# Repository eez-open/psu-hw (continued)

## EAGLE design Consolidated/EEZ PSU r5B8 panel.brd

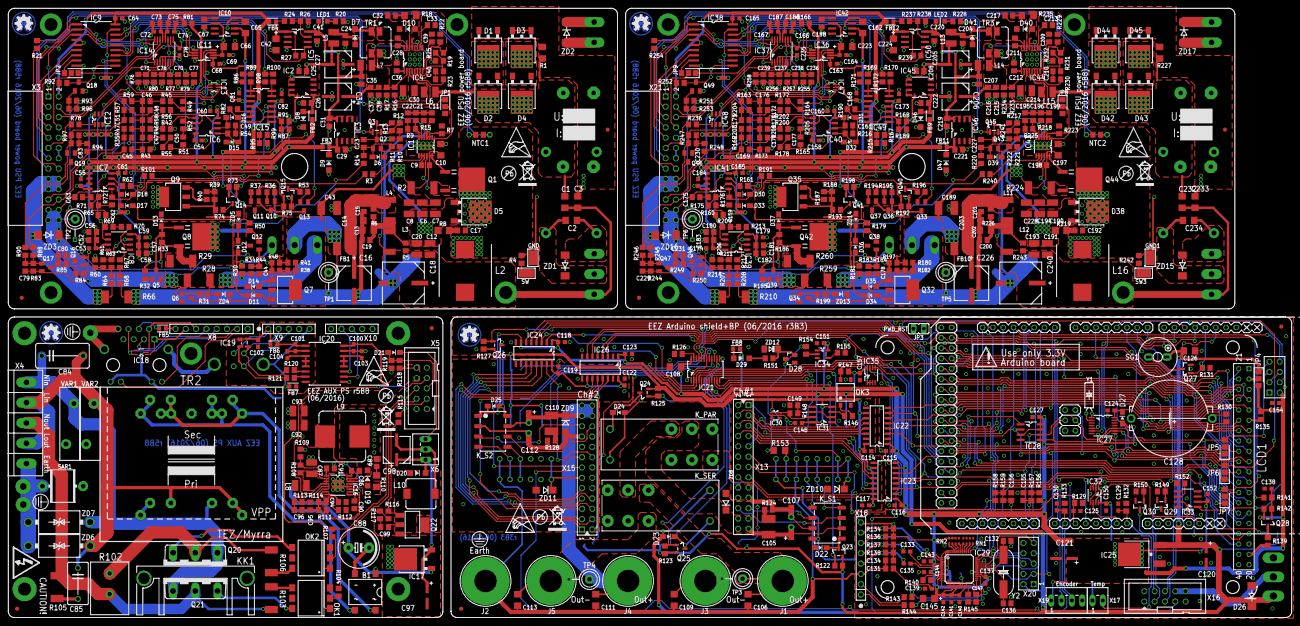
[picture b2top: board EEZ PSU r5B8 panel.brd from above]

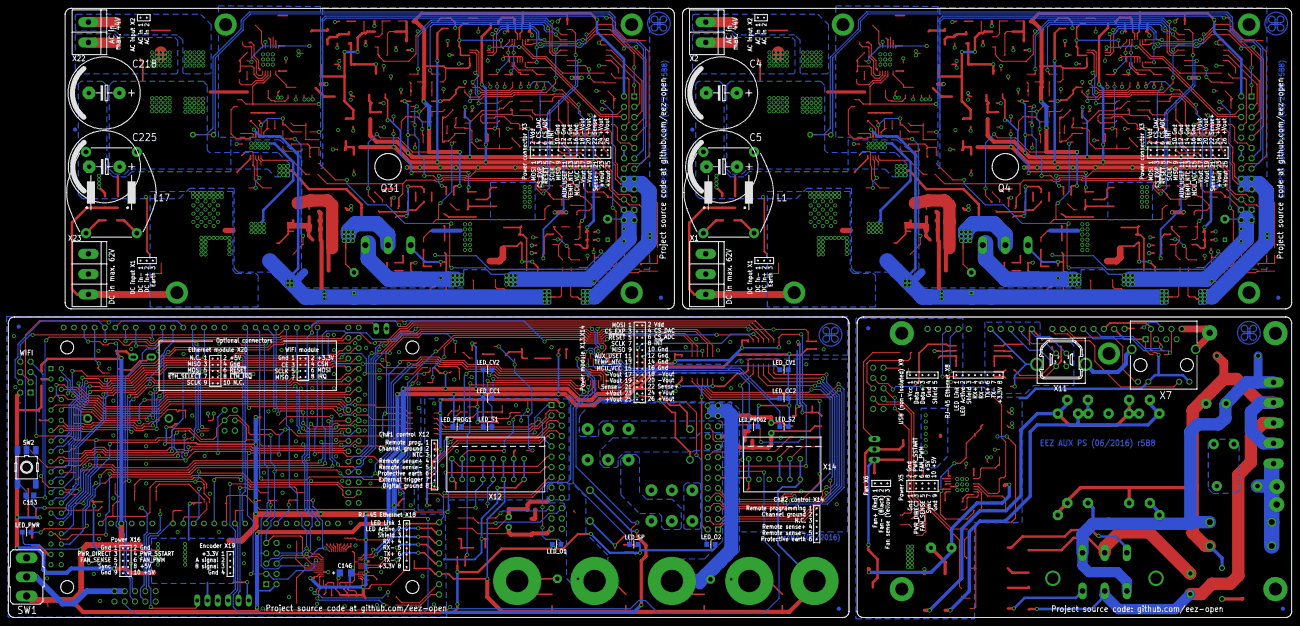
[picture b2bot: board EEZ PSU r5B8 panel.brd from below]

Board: 3 copper layers, 316.0 x 150.0 mm, 809 parts (28 on the bottom side), 562 nets.

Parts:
B1: DF01S; DFS
C1, C2, C3, C232, C233, C234: 100n; C1206
C4, C5, C218, C225: 2m2; ECAP7.5/18
C6, C7, C8, C87, C92, C93, C190, C194, C228: 4u7; C1210
C9, C198: 470n; C0805
C10, C13, C14, C197, C202, C203: 1u; C1206
C11, C15, C19, C26, C29, C36, C41, C91, C199, C200, C201, C212, C220, C221, C222: 100n; C0805
C12, C20, C191, C193: 10u; C1210
C16, C226: EEEFK1J470P; CAPAE830X1050N
C17, C32, C89, C192, C217: 330p; C0805
C18, C240: EEEFK1J101P; PANASONIC_F
C21, C49, C161, C196: 120p; C0805
C22, C195: 4n7; C0805
C23, C227: 470p; C0805
C24, C35, C37, C38, C204, C207, C215, C216: 2u2; C0805
C25, C31, C208, C219: 330n; C0805
C27, C34, C205, C206: 47u; CAPAE660X610N
C28, C86, C90, C131, C211: 22n; C0805
C30, C214: 2u2/100V; C1210
C33, C44, C52, C57, C79, C83, C134, C147, C155, C156, C178, C181, C183, C213, C229, C230: 10n; C0805
C39, C70, C71, C76, C77, C209, C236, C237, C238, C239: 3n3; C0805
C40, C46, C50, C62, C63, C94, C159, C175, C176, C177, C210: 1n; C0805
C42, C146, C224: 4u7; EC1206
C43, C189: 470n; C1812
C45, C51, C169, C171: 47p; C0805
C47, C48, C80, C170, C172, C231: 2n2; C0805
C53, C54, C55, C59, C60, C61, C64, C68, C69, C72, C74, C78, C81, C82, C100, C101, C102, C103, C104, C114, C115, C116, C117, C118, C119, C122, C123, C124, C125, C127, C129, C130, C137, C138, C139, C140, C141, C142, C143, C144, C148, C150, C151, C152, C154, C157, C158, C160, C163, C164, C165, C166, C167, C168, C173, C174, C179, C184, C185, C235: 100n; C0603
C56, C58, C67, C73, C75, C180, C182, C186, C187, C188: 1u; C0805
C65, C108, C126, C162: 10u; C1206
C66, C145, C223: 10u; EC1206
C84: 6n8 (X1); C102-064X133
C85: 47n/400V; C075-052X106
C88: 1mF/25V; ECAP5/10.5
C95: 3n9; C0805
C96: 180p; C0805
C97, C121: 10u; PANASONIC_C
C98: 100u; CAPAE660X610N
C99, C149, C153: 47n; C0805
C105, C110: 470n/100V; C1812
C106, C109, C111, C113: 10n; C1206
C107, C112: UPW1J150MED; CAPAE660X610N_COMBO2
C120: 47u; PANASONIC_C
C128: EECS5R5H105; SG-R20MM
C132, C136: 18p; C0805
C133, C135: 6n8; C0603
D1, D2, D3, D4, D42, D43, D44, D45: STPS15H100; TO252@1
D5, D38: STPS15H100; TO252
D6, D11, D12, D13, D14, D15, D16, D17, D18, D21, D22, D23, D24, D25, D27, D30, D31, D32, D33, D34, D35, D36, D37, D39: BAS316; SOD323-W
D7, D10, D19, D40, D41: DFLS1100-7; SOD123
D8, D9, D20, D29, D46, D47: SKL16; SOD123
D26: SMBJ5.0A-TR; DO214AA
D28: BAT54S; SOT23
EEZ_SIGNATURE, EEZ_SIGNATURE1, EEZ_SIGNATURE2, EEZ_SIGNATURE3: SIGNATURESMALL; SIGNATURE_5MM
FB1, FB10: 2743019447; L1812
FB2, FB3, FB4, FB5, FB6, FB7, FB8, FB9, FB11, FB12: 60R@100MHz; BEAD0603
GND, GND1: S1751-46R
IC1, IC43: LTC3864; LTC_05-08-1666
IC2, IC45: MC79L05; SOIC127P600X173-8N
IC3, IC46: MC78L05; SOIC127P600X173-8N
IC4, IC44: LM5574; SOP65P640X110-16N
IC5, IC50: LP2951SO8; SOIC127P600X175-8N
IC6, IC7, IC40, IC41: TL072D; SOIC127P600X173-8N
IC8, IC39: OP27GSZ; SOIC127P600X173-8N
IC9, IC38: MCP23S08-E/SO; SOIC127P1030X265-18N
IC10, IC42: REF5025; SOIC127P600X175-8N
IC11, IC36: DAC8552; DGK8-M
IC12, IC48: ADG465SOT-23; SOT95P280X145-6N
IC13, IC47: TS5A9411DCKT; SOT65P210X110-6N
IC14, IC37: ADS1120; PW(R-PDSO-G16)
IC15, IC49: LP339D; SOIC127P600X175-14N
IC16: LM25575; SOP65P640X110-17N
IC17: MC7812; TO252
IC18: TPD4E002DRLR; SOT50P280X60-5N
IC19: TPD2E001DZDR; SOP192P292X122-4N
IC20: ADUM3160BRWZ; SOIC-16W
IC21: TLC5925IDBQR; SOP63P600X175-24N
IC22, IC26: Si8641EC-B-IS1; SOIC-16
IC23, IC24: SI8651EC-B-IS1; SOIC-16
IC25: LD1117ADT33TR; DPACK
IC27: PCA21125; SOP65P640X120-14N
IC28: AT25256B; SOIC127P600X175-8N
IC29: W5500; TQFP48-7X7
IC30: BC857BS; SOT65P210X110-6N
IC31: TLC555; SOIC127P600X175-8N
IC32: SN74LVC2G08DCTR; SOP65P400X130-8N
IC33: TPS3705-33D; SOIC127P600X175-8N
IC34: SN74LV1T34DBVR; SOT95P280X145-5N
IC35: SN74LVC2G02DCTR; SOP65P400X130-8N
J1, J4: BS-244DSM-R; BP_5_12
J2: BS-244DSM-G; BP_5_12
J3, J5: BS-244DSM-B; BP_5_12
JP1, JP2, JP4, JP5, JP6, JP7, JP8, JP9: 0R-JUMPA; A0R-JMP
JP3: 826926-2; JP1
KK1: SK 145/37,5; SK145
K_PAR: RT424005; RT-C/016A5_ROUND
K_S1, K_S2: G6K-2F-5DC; G6K-2F
K_SER: RT424005; RT-C/016A5_ROUND
L1, L17: RN114-4/02; RN114
L2, L16: 7443551331; WE-HCI_1350/1365
L3, L4, L11, L12: IHLP2020CZER3R3M11; IHLP-2020BZ-11
L5, L6, L7, L8, L13, L14, L15: 2u2; L1210
L9: 100uH (MSS1260-104K); MSS1278
L10: 470u; DE0704
LCD1: TFT_320QVT; LCD_TFT_320QVT_MIRROR
LED1, LED2: HSMY-C170; LED_0805
LED_CC1, LED_CC2: HSMH-C170; LED_0805
LED_CV1, LED_CV2: HSMY-C170; LED_0805
LED_O1, LED_O2: HSMG-C170; LED_0805
LED_PROG1, LED_PROG2: HSMH-C170; LED_0805
LED_PWR: HSMR-C170; LED_0805
LED_S1, LED_S2: HSMY-C170; LED_0805
LED_SP: HSMH-C170; LED_0805
MCU: Arduino Due; ARDUINO+ICSP_MIRROR
NTC1, NTC2: 10K/Beta:3570K; R_0204/5+0805
OK1: MOC3052; DIL6-SMD
OK2: MOC3062; DIL6-SMD
OK3: HCPL-181
Q1, Q44: SUD19P06-60; TO229P990X239-3N
Q2, Q10, Q11, Q17, Q36, Q37, Q43, Q47: MMBT5401; SOT23-BEC
Q3, Q15, Q27, Q29, Q30, Q40, Q45: 2N7002; SOT103P240X110-3N
Q4, Q31: IRFP250N; TO247BH-CLR
Q5, Q39: BC857C; SOT23-BEC
Q6, Q34: BC846C; SOT23-BEC
Q7, Q9, Q32, Q35: BCP56-16.115; SOT230P700X180-4N
Q8, Q42: IRFR5410; TO229P990X239-3N
Q12, Q13, Q16, Q18, Q19, Q33, Q38, Q46, Q48, Q49: MMBT5551; SOT23-BEC
Q14, Q41: BSS84P; SOT95P237X112-3N
Q20, Q21: BTA26-600; TOP3S-1
Q22: IRLL014N; SOT223
Q23, Q24, Q25, Q26, Q28: IRLML2246TRPBF; SOT95P237X112-3N
R1, R227: 12K; R1206
R2, R224: R010/2W; R2512
R3, R13, R21, R54, R152, R216, R240, R241, R254: 0R; R0805
R4, R31, R39, R78, R117, R154, R155, R188, R199, R236, R242: 1K; R0805
R5, R6, R41, R115, R151, R180, R226, R243: 100R; R0805
R7, R84, R85, R87, R96, R116, R189, R223, R249, R250, R253: 47K; R0805
R8, R18, R110, R219, R235: 10R; R1206
R9, R10, R27, R43, R49, R51, R58, R72, R74, R82, R92, R93, R95, R101, R119, R135, R141, R145, R157, R159, R164, R165, R173, R174, R176, R190, R191, R193, R215, R221, R225, R239, R251, R252: 10K; R0805
R11, R14, R46, R56, R73, R75, R125, R131, R142, R192, R198, R201, R202, R220, R222: 100K; R0805
R12, R217: 324K; R0805
R15, R218: 4K32; R0805
R16, R233: 39K; R0805
R17, R53, R196, R234: 1K8; R0805
R19, R149, R150, R231: 30K; R0805
R20, R228: 390R; R0805
R22, R47, R57, R113, R203, R204, R229: 20K; R0805
R23, R48, R197, R230: 51K; R0805
R24, R99, R167, R237: 12K; R0805
R25, R122, R123, R127, R129, R132, R133, R156, R158, R232: 4K7; R0805
R26, R238: 3K9; R0805
R28, R259: R080/3W; R2512
R29, R260: 2R2/2W; R2512
R30, R32, R33, R62, R65, R91, R109, R160, R161, R168, R181, R185, R186: 2K2; R0805
R34, R183: 16K; R0805
R35, R59, R162, R163: 2K; R0805
R36, R37, R40, R45, R55, R76, R77, R79, R80, R177, R178, R187, R194, R195, R255, R256, R257, R258: 220R; R0805
R38, R50, R179, R182: 470R; R0805
R42, R52, R200, R205: 7K5; R0805
R44, R184: 560R; R0805
R60, R70, R213, R214: 180R 0.1%; R0805
R61, R69, R206, R209: 3K9 0.1%; R0805
R63, R64, R67, R68, R207, R208, R211, R212: 51R 0.1%; R0805
R66, R210: R020/2W; R2512
R71, R175: 11K; R0805
R81, R139, R166: 10R; R0805
R83, R97, R244, R247: 330R; R0805
R86, R98, R171, R172: 5K1; R0805
R88, R94, R245, R248: 750R; R0805
R89, R100, R118, R169, R170: 5K6; R0805
R90, R246: 3K3; R0805
R102: 15R/7W; R_0913
R103, R106: 330R/2W; R2512
R104, R107: 270R; R0805
R105: 150R/2W; R2512
R108: 15K; R0805
R111: 5K6 1%; R0805
R112: 18K; R0805
R114: 1K8 1%; R0805
R120, R121: 22R; R0805
R124, R128: 1R; R0805
R126, R147, R148: 1K5; R0805
R130, R143, R144, R146: 180R; R0805
R134, R136, R137, R138: 49R9; R0805
R140: 12K4; R0805
R153: 10K; R1206
RN1, RN2: 4x10K; CAY16
SAR1: CG2-470L; SAR
SG1: LD-BZEN-0903; BUZZER
SH1, SH4: Pgnd to Pout- short; SHORT_NOHOLE
SH2, SH5: Sgnd to Pgnd short; SHORT_NOHOLE
SH3: SHORT_NOHOLE
SW, SW3: S1751-46R
SW1: A101SYCQ04; M9040P
SW2: 1301.9316; TACTM-6XN
TP1, TP2, TP3, TP4, TP5, TP6: TP_1.1MM
TR1, TR3: SRF0703-821M; SRF0703
TR2: TEZ6/D230/15V; PCB_TRAFO6VA_7.5W
U$1, U$2, U$8, U$17: RECYCLE_BIN1/8
U$3, U$5, U$9, U$18: PB_SMALL
U$4, U$6, U$7, U$10: ESD_SYMBOL
U$11, U$12, U$13, U$14, U$15, U$16, U$19, U$20: FIDUCIAL_2; FIDUCIAL_DUAL
VAR1, VAR2: S20K250; VARISTOR
WIFI: NRF24L01 module; MOD-NRF24L01_MIRROR
X1, X23: 282836-3; TBLOCK5.0_3
X2, X22: 282836-2; TBLOCK5.0_2
X3, X21: SSW-113-02-T-D-RA
X4: 282836-5; TBLOCK5.0_5
X5, X16: 09185067324; IDC-10PIN
X6: 22-23-2031
X7: LMJ2138812S0LOT6C; RJ45-VERT
X8, X18: 826629-8; SSW-108-02-S-S
X9, X10: 826629-5; SSW-105-02-S-S
X11: 2411-01; KUSBVX-BS1N
X12: MC000006; MC000006_MIRROR
X13, X15: TSW-113-07-F-D
X14: MC000005; MC000005_MIRROR
X17: 22-23-2021
X19: 22-23-2041
X20: SSW-105-02-S-D
Y1: 32,768kHz; R26_XTAL
Y2: 25MHz; HC-49/4H
ZD1, ZD2, ZD15, ZD17: n.c.; DO214AA
ZD3, ZD16: See Note 3.2; DO214AA
ZD4, ZD13: BZX384-C15.115; SOD323-W
ZD5, ZD14: PDZ6.2B; SOD323-W
ZD6, ZD7: 1.5KE400CA; DO201-BIDIR
ZD8, ZD9: P4SMAJ60A; DO214AC
ZD10, ZD11: SMAJ18A; DO214AC
ZD12: 4V3; MINIMELF

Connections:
1V2O: C147.2, IC29.22
12VDC: C97.1, C98.1, D20.C, IC17.2, X6.1
!ADC1_SELECT: IC23.4, MCU.15
!ADC2_SELECT: IC26.4, MCU.48
!BP_OE: IC21.21, MCU.10
!BP_OUT0: IC21.5, LED_CV1.C
!BP_OUT1: IC21.6, Q23.1, R122.1
!BP_OUT2: IC21.7, LED_O1.C
!BP_OUT3: IC21.8, LED_SP.C
!BP_OUT4: IC21.9, LED_PROG1.C
!BP_OUT5: IC21.10, LED_S1.C
!BP_OUT6: IC21.11, LED_CC1.C
!BP_OUT7: IC21.12, LED_CV2.C
!BP_OUT8: IC21.13, Q25.1, R123.1
!BP_OUT9: IC21.14, Q24.1, R125.1
!BP_OUT10: IC21.15, LED_CC2.C
!BP_OUT12: IC21.17, LED_S2.C
!BP_OUT13: IC21.18, LED_O2.C
!BP_OUT14: IC21.19, Q26.1, R127.1
!BP_OUT15: IC21.20, LED_PWR.C
!CH1_ADC: IC23.13, X13.6
!CH1_DAC: IC22.12, X13.4
!CH1_EXPANDER: IC22.13, X13.3
!CH1_INT: IC23.11, X13.8
!CH1_RESET: IC23.14, X13.5
!CH2_ADC: IC26.13, X15.6
!CH2_DAC: IC24.12, X15.4
!CH2_EXPANDER: IC24.13, X15.3
!CH2_INT: IC24.11, X15.8
!CH2_RESET: IC26.14, X15.5
!CONVEND1: IC23.6, MCU.21
!CONVEND2: IC24.6, MCU.20
!DAC1_SELECT: IC22.5, MCU.16
!DAC2_SELECT: IC24.5, MCU.47
!DP_DRIVE: Q9.1, R39.1, R74.1
!DP_DRIVE1: Q35.1, R188.1, R193.1
!EEPROM_SELECT: IC28.1, MCU.49
!ETH_IRQ: IC29.36, MCU.18, WIFI.8, X20.8
!ETH_SELECT: IC29.32, MCU.11, WIFI.4, X20.7
!INT: JP2.2, X3.8
!INT1: JP9.2, X21.8
!IO_EXPANDER1: IC22.4, MCU.17
!IO_EXPANDER2: IC24.4, MCU.46
!MR: C153.2, IC33.1, SW2.3, SW2.4
!PS_DRDY: IC14.14, JP2.3
!PS_DRDY1: IC37.14, JP9.3
!PS_RESET: IC9.6, X3.5
!PS_RESET1: IC38.6, X21.5
!PWD_RST: JP3.1, MCU.A13
!RESET: IC23.3, IC26.3, IC29.37, IC32.2, IC32.5, IC33.7, MCU.RESET, X20.6
!RTC_IRQ: IC27.5, MCU.19
!SET_100%: IC9.13, Q3.1
!SET_100%1: IC38.13, Q45.1
!SET_DP: IC9.11, Q14.1, R73.2
!SET_DP1: IC38.11, Q41.1, R198.2
+3V3: C108.1, C115.1, C116.1, C118.1, C121.1, C123.1, C127.1, C131.1, C137.2, C139.1, C140.1, C141.1, C142.1, C143.1, C144.1, C145.+, C150.2, C151.1, C152.2, C154.1, C157.1, D27.A, IC21.24, IC22.1, IC23.1, IC23.7, IC24.1, IC24.7, IC25.4, IC26.1, IC28.3, IC28.7, IC28.8, IC29.4, IC29.8, IC29.11, IC29.15, IC29.17, IC29.21, IC29.28, IC32.8, IC33.2, IC34.5, IC35.8, JP4.3, Q28.2, R134.1, R135.2, R136.2, R142.2, R147.1, R156.1, R158.1, RN2.6, RN2.7, RN2.8, WIFI.2, X13.15, X15.15, X17.1, X18.8, X19.1
+5V: C64.1, C68.2, C72.2, C73.2, C92.1, C93.1, C100.1, C120.1, C126.2, D26.C, FB4.P$2, FB8.P$1, IC9.18, IC11.1, IC14.13, IC16.11, IC20.16, IC25.3, JP4.1, L9.2, LED_CC1.A, LED_CC2.A, LED_CV1.A, LED_CV2.A, LED_O1.A, LED_O2.A, LED_PROG1.A, LED_PROG2.A, LED_PWR.A, LED_S1.A, LED_S2.A, LED_SP.A, MCU.5V, OK1.1, OK2.1, Q13.B, Q14.2, Q23.2, Q24.2, Q25.2, Q26.2, R73.1, R86.2, R92.2, R98.2, R111.1, R118.1, R122.2, R123.2, R125.2, R127.2, SG1.+, SG1.+B, SW1.3, X3.2, X5.8, X5.10, X20.2
+5V1: C163.2, C165.1, C167.2, C187.2, FB12.P$2, IC36.1, IC37.13, IC38.18, Q33.B, Q41.2, R171.2, R172.2, R198.1, R252.2, X21.2
+VNR: C31.1, C35.1, C41.1, IC3.8, IC5.8, L7.2, LED1.A
+VNR1: C207.1, C219.1, C220.1, IC46.8, IC50.8, L14.2, LED2.A
+VREF: C66.+, C69.2, C78.2, IC10.6, IC11.2, IC14.9
+VREF1: C164.2, C223.+, C235.2, IC36.2, IC37.9, IC42.6
-9V: C25.2, C27.2, IC2.2, IC2.3, IC2.6, IC2.7, L5.2, R39.2, R40.2
-9V1: C205.2, C208.2, IC45.2, IC45.3, IC45.6, IC45.7, L13.2, R187.2, R188.2
AC_EARTH: FB7.P$1, SAR1.P$2, X4.5, X7.8, X7.SH1, X7.SH2, X9.5, X11.M1, X11.M2, ZD6.C, ZD7.C
AC_IN1: D3.3, D4.1, D4.2, X2.1, ZD2.A
AC_IN1_MAIN: C84.1, Q20.A1, Q21.A1, TR2.P1.2V, TR2.P2.2V, TR2.P2_TEZ, VAR1.P$2, X4.1, ZD7.A
AC_IN2: D1.3, D2.1, D2.2, X2.2, ZD2.C
AC_IN2_MAIN: C84.2, C85.1, TR2.P1.1V, TR2.P1_TEZ, TR2.P2.1V, VAR2.P$1, X4.2, X4.4, ZD6.A
AC_IN3: D42.1, D42.2, D44.3, X22.2, ZD17.C
AC_IN4: D43.1, D43.2, D45.3, X22.1, ZD17.A
AUX1_USET_IN: X12.8, X12.8.1, X13.11, ZD10.C
AUX2_USET_IN: X14.6, X14.6.1, X15.11, ZD11.C
AUX_+3V3: FB5.P$2, X8.8
AUX_ETH_ACTLED: X7.YA, X8.2
AUX_ETH_IN+: IC18.5, X7.6, X8.4
AUX_ETH_IN-: IC18.4, X7.3, X8.5
AUX_ETH_LINKLED: X7.GA, X8.1
AUX_ETH_OUT+: IC18.3, X7.2, X8.6
AUX_ETH_OUT-: IC18.1, X7.1, X8.7
AUX_FAN_CTRL: R115.2, X5.6
AUX_FAN_SENSE: D21.A, R118.2, R119.1, X5.5
AUX_PWR_DIRECT: R104.2, X5.3
AUX_PWR_SSTART: R107.2, X5.4
AUX_USET_IN: R78.2, X3.11
AUX_USET_IN1: R236.2, X21.11
AUX_USET_SW: IC9.14, IC13.1
AUX_USET_SW1: IC38.14, IC47.1
BATT_NTC: MCU.A4, OK3.4, R147.2
BP_SELECT: IC21.4, MCU.9
BUZZER: MCU.12, Q27.1, R131.2
CC_ACTIVE: IC9.12, R98.1, R100.2
CC_ACTIVE1: IC38.12, R170.2, R172.1
CH1_GND: C114.2, C117.2, C148.2, C149.1, IC22.9, IC22.15, IC23.9, IC31.1, OK3.2, X12.6, X12.6.1, X13.10, X13.12, X13.14, ZD10.A
CH1_MISO: IC22.11, X13.9
CH1_MOSI: IC22.14, X13.1
CH1_SCLK: IC23.12, X13.7
CH1_SYNC: IC23.15, X13.16
CH1_VDD: C114.1, C117.1, C148.1, IC22.10, IC22.16, IC23.10, IC23.16, IC30.1, IC30.4, IC31.4, IC31.8, X13.2
CH2_GND: C119.2, C122.2, IC24.9, IC26.9, IC26.15, X14.5, X14.5.1, X15.10, X15.12, X15.14, ZD11.A
CH2_MISO: IC26.11, X15.9
CH2_MOSI: IC24.14, X15.1
CH2_SCLK: IC26.12, X15.7
CH2_SYNC: IC24.15, X15.16
CH2_VDD: C119.1, C122.1, IC24.10, IC24.16, IC26.10, IC26.16, X15.2
CS_ADC: IC14.2, X3.6
CS_ADC1: IC37.2, X21.6
CS_DAC: IC11.5, X3.4
CS_DAC1: IC36.5, X21.4
CS_EXPANDER: IC9.7, X3.3
CS_EXPANDER1: IC38.7, X21.3
CV_ACTIVE: IC9.15, R86.1, R89.2
CV_ACTIVE1: IC38.15, R169.2, R171.1
D+: IC19.2, R121.1, X9.3, X11.3
D-: IC19.3, R120.1, X9.2, X11.2
DC+: C2.2, L1.2, X1.2, ZD1.C
DC+1: C234.2, L17.2, X23.2, ZD15.C
DC-: C2.1, L1.1, X1.3, ZD1.A
DC-1: C234.1, L17.1, X23.3, ZD15.A
DC_OUT: C1.2, C4.+, C5.+, C6.1, C7.1, C8.1, C9.2, C10.1, C43.1, D2.3, D4.3, IC1.11, L1.3, L6.1, Q7.2, Q7.4, R1.1, R2.1, R36.2, R37.2
DC_OUT1: C189.1, C190.1, C194.1, C197.1, C198.2, C218.+, C225.+, C228.1, C232.2, D42.3, D43.3, IC43.11, L15.1, L17.3, Q32.2, Q32.4, R194.2, R195.2, R224.1, R227.1
DC_PREG1: C30.1, IC4.3, L6.2, R16.2
DC_PREG2: C87.1, IC16.3, L8.2, R108.2
DC_PREG3: C214.1, IC44.3, L15.2, R233.2
DP_LED: Q14.3, R74.2
DP_LED1: Q41.3, R193.2
EARTH: C1.1, C3.2, C106.2, C109.1, C111.2, C113.1, C131.2, C134.2, J2.P$1, X1.1, X12.3, X12.3.1, X14.1, X14.1.1, X18.3
EARTH1: C232.1, C233.2, X23.1
ENC_A: C155.2, MCU.A8, R157.1
ENC_B: C156.1, MCU.A9, R159.1
ETH_ACTLED: IC29.27, R143.1
ETH_IN+: C135.1, R138.1, X18.4
ETH_IN-: C133.1, R137.2, X18.5
ETH_LINKLED: IC29.25, R144.1
ETH_OUT+: IC29.2, R136.1, X18.6
ETH_OUT-: IC29.1, R134.2, X18.7
EXT_TRIG: MCU.A7, R155.1
FAN_OUT: C99.2, D20.A, L10.2, Q22.2, Q22.4
FAN_PWM: MCU.6, X16.6
FAN_SENSE: MCU.13, X16.5
FB: IC1.5, Q3.2, R12.2, R13.2, R15.1
FB1: IC43.5, Q45.2, R217.2, R218.1, R241.2
GND: B1.-, C3.1, C4.-, C5.-, C6.2, C7.2, C8.2, C10.2, C12.2, C18.2, C20.2, C24.2, C25.1, C26.1, C27.1, C29.2, C30.2, C31.2, C33.2, C34.2, C35.2, C36.1, C37.2, C38.2, C39.1, C41.2, C42.-, C43.2, C44.2, C52.1, C53.2, C54.1, C55.1, C56.1, C57.1, C58.1, C59.2, C60.1, C61.1, C64.2, C65.2, C66.-, C67.2, C68.1, C69.1, C70.1, C71.2, C72.1, C73.1, C74.1, C75.1, C76.1, C77.1, C78.1, C81.1, C82.1, C87.2, C88.-, C90.2, C91.1, C92.2, C93.2, C94.1, C97.2, C100.2, C103.2, C108.2, C115.2, C116.2, C118.2, C120.2, C121.2, C123.2, C124.1, C125.1, C126.1, C127.2, C128.2, C129.1, C130.1, C132.2, C136.2, C137.1, C138.1, C139.2, C140.2, C141.2, C142.2, C143.2, C144.2, C145.-, C147.1, C150.1, C151.2, C152.1, C153.1, C154.2, C155.1, C156.2, C157.2, D1.1, D1.2, D3.1, D3.2, D5.1, D5.2, D8.C, D9.A, D22.A, D23.A, D24.A, D25.A, D26.A, D28.1, GND.P$1, IC1.TP, IC2.5, IC3.2, IC3.3, IC3.6, IC3.7, IC4.9, IC4.12, IC5.4, IC7.5, IC9.4, IC9.5, IC9.9, IC10.4, IC11.8, IC13.3, IC14.3, IC14.4, IC14.5, IC14.8, IC16.9, IC16.12, IC16.TP, IC17.3, IC18.2, IC20.9, IC20.15, IC21.1, IC22.2, IC22.8, IC23.8, IC24.8, IC25.1, IC26.2, IC26.8, IC27.7, IC28.4, IC29.29, IC32.4, IC33.3, IC33.4, IC34.3, IC35.4, JP3.2, K_PAR.A1, K_S1.8, K_S2.8, K_SER.A1, L1.4, LCD1.1, MCU.GND, MCU.GND1, MCU.GND2, MCU.GND3, MCU.GND4, MCU.ICSP_GND, OK3.3, Q8.2, Q15.2, Q16.E, Q18.E, Q22.3, Q27.2, Q29.2, Q30.2, R1.2, R8.1, R17.1, R20.2, R22.2, R25.2, R26.2, R42.1, R44.1, R48.1, R60.1, R75.1, R84.1, R91.1, R95.2, R96.1, R109.1, R112.2, R114.2, R116.1, R117.1, R119.2, R126.1, R129.2, R131.1, R132.2, R133.2, R145.1, R149.2, R150.2, RN1.5, RN1.6, RN1.7, RN1.8, RN2.5, SH1.P$2, SH2.P$2, SH3.P$1, SW2.1, SW2.2, SW2.5, TP2.GND, TR1.4, WIFI.1, X3.10, X3.12, X3.14, X5.1, X5.2, X5.9, X7.GC, X7.YC, X12.1, X12.1.1, X16.1, X16.2, X16.9, X19.4, X20.4, ZD12.A
GND1: C158.1, C160.1, C162.2, C163.1, C164.1, C165.2, C166.1, C167.1, C168.1, C173.1, C174.2, C178.2, C179.2, C180.1, C181.1, C182.1, C183.1, C184.1, C185.1, C186.1, C187.1, C188.2, C189.2, C190.2, C191.2, C193.2, C194.2, C197.2, C204.2, C205.1, C206.2, C207.2, C208.1, C209.1, C212.1, C213.2, C214.2, C215.2, C216.2, C218.-, C219.2, C220.2, C221.2, C222.1, C223.-, C224.-, C225.-, C228.2, C233.1, C235.1, C236.1, C237.1, C238.1, C239.2, C240.2, D38.1, D38.2, D44.1, D44.2, D45.1, D45.2, D46.C, D47.A, GND1.P$1, IC36.8, IC37.3, IC37.4, IC37.5, IC37.8, IC38.4, IC38.5, IC38.9, IC41.5, IC42.4, IC43.TP, IC44.9, IC44.12, IC45.5, IC46.2, IC46.3, IC46.6, IC46.7, IC47.3, IC50.4, L17.4, Q40.2, Q42.2, Q48.E, Q49.E, R168.1, R184.1, R192.1, R197.1, R200.1, R214.1, R215.2, R219.1, R227.2, R228.2, R229.2, R232.2, R234.1, R238.2, R250.1, R253.1, SH4.P$2, SH5.P$2, TP6.GND, TR3.4, X21.10, X21.12, X21.14
GNDA: C146.-, IC29.3, IC29.9, IC29.14, IC29.16, IC29.19, IC29.48, R140.1, SH3.P$2
INT_EXP: IC9.8, JP2.1
INT_EXP1: IC38.8, JP9.1
IS: D10.A, IC4.13, R18.1
IS1: D19.A, IC16.13, R110.1
IS2: D40.A, IC44.13, R235.1
ISENSE+: IC8.3, R61.2, R63.2
ISENSE+1: IC39.3, R206.2, R211.2
ISENSE-: IC8.2, R67.2, R70.1
ISENSE-1: IC39.2, R212.2, R213.1
ISOLATOR1_EN: IC22.7, MCU.14
ISOLATOR2_EN: IC26.7, MCU.45
I_MON: IC8.6, R65.1, R69.2, R80.1
I_MON1: IC39.6, R160.1, R209.2, R256.1
I_SERVO: C62.2, D17.C, D18.A, IC7.1, R101.1
I_SERVO1: C159.2, D30.A, D33.C, IC41.1, R191.1
I_SET: IC11.3, R62.1, R76.1
I_SET1: IC36.3, R161.1, R258.1
LCDSD_CS: LCD1.38, MCU.53
LCD_BRIGHTNESS: MCU.7, R141.1
LCD_CS: LCD1.15, MCU.39
LCD_DB0: LCD1.21, MCU.37
LCD_DB1: LCD1.22, MCU.36
LCD_DB2: LCD1.23, MCU.35
LCD_DB3: LCD1.24, MCU.34
LCD_DB4: LCD1.25, MCU.33
LCD_DB5: LCD1.26, MCU.32
LCD_DB6: LCD1.27, MCU.31
LCD_DB7: LCD1.28, MCU.30
LCD_DB8: LCD1.7, MCU.22
LCD_DB9: LCD1.8, MCU.23
LCD_DB10: LCD1.9, MCU.24
LCD_DB11: LCD1.10, MCU.25
LCD_DB12: LCD1.11, MCU.26
LCD_DB13: LCD1.12, MCU.27
LCD_DB14: LCD1.13, MCU.28
LCD_DB15: LCD1.14, MCU.29
LCD_RD: LCD1.6, R135.1
LCD_RESET: LCD1.17, MCU.38
LCD_RS: LCD1.4, MCU.41
LCD_WR: LCD1.5, MCU.40
LED_A: LCD1.19, R139.2
L_OUT: C12.1, C18.1, C20.1, L2.2, L3.1, R5.1, R10.1, R11.1, R12.1
L_OUT12: C191.1, C193.1, C240.1, L12.1, L16.2, R217.1, R221.1, R222.1, R243.1
MCU_D+: IC20.10, X10.3
MCU_D-: IC20.11, X10.2
MCU_VCC: NTC1.2, NTC1.2.1, X3.15
MCU_VCC1: NTC2.2, NTC2.2.1, X21.15
MISO: IC22.6, IC26.6, IC27.8, IC28.2, IC29.34, JP7.1, LCD1.35, MCU.ICSP_MISO, WIFI.7, X20.3
MODE: IC1.1, JP1.2
MODE1: IC43.1, JP8.2
MOSI: IC21.2, IC22.3, IC24.3, IC27.9, IC28.5, IC29.35, JP6.1, LCD1.37, MCU.ICSP_MOSI, WIFI.6, X20.5
unnamed: Q9.3, R40.1
unnamed: Q5.B, R32.2
unnamed: C45.2, R43.1
unnamed: C26.2, D8.A, FB2.P$1, IC2.1
unnamed: C29.1, D9.C, FB3.P$1, IC3.1
unnamed: C42.+, FB4.P$1, IC5.1, R24.1, R27.1
unnamed: R4.2, SW.P$1
unnamed: R63.1, R64.2
unnamed: IC12.4, IC13.6
unnamed: C51.2, R58.1
unnamed: C67.1, IC10.5
unnamed: IC12.1, R78.1
unnamed: R67.1, R68.2
unnamed: R69.1, R70.2
unnamed: R60.2, R61.1
unnamed: IC7.6, IC7.7
unnamed: C48.1, R56.2, R57.1
unnamed: C49.2, R54.1
unnamed: D6.C, Q2.E, R10.2
unnamed: C21.1, IC1.6, R9.2
unnamed: C22.1, R9.1
unnamed: C63.2, R72.1
unnamed: C9.1, IC1.9
unnamed: R21.2, X3.16
unnamed: C79.2, Q17.B, R83.1, R88.2, R90.2
unnamed: C46.2, R45.1
unnamed: C50.2, R55.1
unnamed: C77.2, IC14.10, R79.2
unnamed: IC6.3, R45.2, R49.2
unnamed: IC1.12, Q1.1
unnamed: IC1.2, R7.1
unnamed: C49.1, D16.C, IC6.2, R51.2, R55.2
unnamed: C11.2, IC1.4
unnamed: C23.1, Q2.C, Q3.3, R13.1
unnamed: C13.1, C19.2, L3.2, L4.1, R5.2, R6.1
unnamed: IC1.8, R3.1
unnamed: D18.C, IC7.2, R65.2, R71.2, R72.2
unnamed: C17.2, R8.2
unnamed: Q18.B, R93.1, R96.2
unnamed: C80.2, Q17.C, R85.1, R93.2
unnamed: C70.2, IC14.11, R77.2
unnamed: C74.2, C75.2, IC14.12, R81.2
unnamed: LED1.C, R20.1
unnamed: Q12.B, R34.1, R44.2
unnamed: IC15.1, IC15.2, R89.1
unnamed: C32.2, R18.2
unnamed: Q19.C, R90.1
unnamed: IC15.13, IC15.14, R100.1
unnamed: C83.1, Q19.B, R94.1, R97.2
unnamed: IC7.3, R62.2
unnamed: C71.1, IC14.6, R76.2
unnamed: C95.2, R113.2
unnamed: C80.1, Q16.B, R84.2, R85.2
unnamed: D15.A, D17.A, R50.1
unnamed: C76.2, IC14.7, R80.2
unnamed: D11.C, D12.A, Q4.G, R30.1
unnamed: C95.1, C96.1, IC16.6, R111.2, R114.1
unnamed: C86.2, IC16.16
unnamed: C96.2, IC16.5, R113.1
unnamed: IC16.7, R112.1
unnamed: C91.2, IC16.1
unnamed: D11.A, Q7.3
unnamed: C94.2, IC16.8
unnamed: IC5.7, R24.2, R26.1
unnamed: D14.A, Q7.1, R38.2, R41.1
unnamed: C90.1, IC16.10
unnamed: C44.1, R38.1
unnamed: IC16.4, X5.7
unnamed: IC16.2, R108.1, R109.2
unnamed: C89.2, R110.2
unnamed: OK1.6, Q21.G
unnamed: OK2.4, Q20.G
unnamed: OK2.6, R106.1
unnamed: OK1.2, R104.1
unnamed: OK2.2, R107.1
unnamed: OK1.4, R103.1
unnamed: C40.2, R23.2
unnamed: B1.AC1, TR2.S1.1T, TR2.S1.1V, TR2.S2.1T, TR2.S2.1V, TR2.S2M
unnamed: C23.2, D6.A, Q2.B, R11.2, R14.1
unnamed: B1.AC2, TR2.S1.2T, TR2.S1.2V, TR2.S1M, TR2.S2.2T, TR2.S2.2V
unnamed: Q20.A2, R102.1, R106.2
unnamed: Q21.A2, R102.2, R103.2, R105.1, X4.3
unnamed: C85.2, R105.2
unnamed: C99.1, R117.2
unnamed: Q22.1, R115.1, R116.2
unnamed: C98.2, L10.1, X6.2
unnamed: C104.1, IC20.3, IC20.4, IC20.5
unnamed: IC20.6, R120.2
unnamed: IC20.7, R121.2
unnamed: C101.1, FB6.P$2, IC20.1
unnamed: C103.1, IC20.12, IC20.13, IC20.14
unnamed: D22.C, K_S1.1, Q23.3
unnamed: D25.C, K_S2.1, Q26.3
unnamed: C105.2, R124.2
unnamed: C110.2, R128.2
unnamed: IC21.16, LED_PROG2.C
unnamed: K_SER.14A, K_SER.14B
unnamed: K_PAR.12A, K_SER.11B
unnamed: K_PAR.12B, K_SER.11A
unnamed: SW1.2, X16.8, X16.10
unnamed: Q27.3, SG1.-, SG1.-B
unnamed: JP4.2, LCD1.2
unnamed: Q28.3, R139.1
unnamed: JP7.2, LCD1.33
unnamed: JP5.2, LCD1.29
unnamed: JP6.2, LCD1.31
unnamed: C128.1, R130.1
unnamed: IC29.23, R145.2
unnamed: C124.2, D27.C, IC27.14, R130.2
unnamed: IC29.10, R140.2
unnamed: C132.1, IC29.31, Y2.1
unnamed: C136.1, IC29.30, Y2.2
unnamed: C133.2, IC29.5
unnamed: SAR1.P$1, VAR1.P$1, VAR2.P$2
unnamed: C135.2, IC29.6
unnamed: R144.2, X18.1
unnamed: C47.1, R46.2, R47.1
unnamed: R143.2, X18.2
unnamed: IC29.43, RN2.3
unnamed: IC29.44, RN2.2
unnamed: IC29.45, RN2.1
unnamed: IC29.42, RN2.4
unnamed: IC29.38, RN1.4
unnamed: C134.1, R137.1, R138.2
unnamed: FB5.P$1, X7.4
unnamed: IC29.39, RN1.3
unnamed: IC29.41, RN1.1
unnamed: C40.1, IC4.6, R19.2, R25.1
unnamed: D14.C, Q6.C, ZD4.C
unnamed: IC29.40, RN1.2
unnamed: C28.2, IC4.16
unnamed: C138.2, Q28.1, R141.2, R142.1
unnamed: IC27.1, Y1.2
unnamed: IC27.2, Y1.1
unnamed: IC4.5, R23.1
unnamed: C149.2, IC31.2, IC31.6, R148.2
unnamed: IC30.6, IC31.7, R148.1
unnamed: OK3.1, R146.2
unnamed: D28.3, R153.2, R154.2
unnamed: IC34.2, R154.1
unnamed: IC34.4, R155.2
unnamed: R153.1, X12.2, X12.2.1
unnamed: D12.C, ZD5.C
unnamed: D28.2, R151.1, ZD12.C
unnamed: Q12.E, R50.2
unnamed: Q8.3, R29.1, R32.1, R33.1
unnamed: D13.A, Q5.C, Q8.1, R33.2
unnamed: D29.C, R151.2
unnamed: D29.A, FB8.P$2
unnamed: IC6.5, R42.2, R43.2, R46.1
unnamed: IC33.6, R152.1
unnamed: IC32.3, Q29.1, R149.1
unnamed: IC15.5, IC15.6, R82.2
unnamed: IC32.7, Q30.1, R150.1
unnamed: D23.C, K_SER.A2, Q25.3
unnamed: D24.C, K_PAR.A2, Q24.3
unnamed: R156.2, R157.2, X19.2
unnamed: IC6.6, R52.2, R56.1, R58.2
unnamed: R158.2, R159.2, X19.3
unnamed: IC15.8, IC15.11, R101.2
unnamed: D21.C, X6.3
unnamed: IC41.3, R161.2
unnamed: IC4.7, R22.1
unnamed: C36.2, IC4.1
unnamed: C39.2, IC4.8
unnamed: C33.1, IC4.10
unnamed: IC40.3, R164.2, R177.2
unnamed: IC15.7, IC15.9, R87.1, R91.2
unnamed: C161.1, D31.C, IC40.2, R165.2, R178.2
unnamed: C62.1, R71.1
unnamed: C166.2, C186.2, IC37.12, R166.2
unnamed: IC49.1, IC49.2, R169.1
unnamed: IC40.5, R173.2, R200.2, R201.1
unnamed: IC40.6, R174.2, R202.1, R205.2
unnamed: IC15.4, IC15.10, R95.1, R99.2
unnamed: C172.1, R202.2, R204.1
unnamed: C24.1, D7.A, L5.1
unnamed: IC4.2, R16.1, R17.2
unnamed: C170.1, R201.2, R203.1
unnamed: C169.2, R173.1
unnamed: Q11.E, R37.1
unnamed: Q10.E, R36.1
unnamed: C171.2, R174.1
unnamed: Q13.E, R53.2
unnamed: C175.2, R176.1
unnamed: D30.C, IC41.2, R160.2, R175.2, R176.2
unnamed: C176.2, R177.1
unnamed: C177.2, R178.1
unnamed: D32.A, D33.A, R179.1
unnamed: D34.C, D36.A, Q31.G, R181.1
unnamed: D34.A, Q32.3
unnamed: D35.A, Q32.1, R180.1, R182.2
unnamed: D35.C, Q34.C, ZD13.C
unnamed: C178.1, R182.1
unnamed: D36.C, ZD14.C
unnamed: Q42.3, R185.1, R186.1, R260.1
unnamed: D37.A, Q39.C, Q42.1, R186.2
unnamed: Q38.E, R179.2
unnamed: Q6.B, R31.1
unnamed: IC49.13, IC49.14, R170.1
unnamed: IC49.5, IC49.6, R190.2
unnamed: IC49.8, IC49.11, R191.2
unnamed: IC49.7, IC49.9, R168.2, R189.1
unnamed: IC49.4, IC49.10, R167.2, R215.1
unnamed: Q37.E, R194.1
unnamed: Q36.E, R195.1
unnamed: Q33.E, R196.2
unnamed: Q38.B, R183.1, R184.2
unnamed: Q34.B, R199.1
unnamed: C159.1, R175.1
unnamed: Q35.3, R187.1
unnamed: Q39.B, R185.2
unnamed: C188.1, IC42.5
unnamed: R207.2, R211.1
unnamed: R208.2, R212.1
unnamed: R209.1, R213.2
unnamed: R206.1, R214.2
unnamed: IC41.6, IC41.7
unnamed: C161.2, R216.1
unnamed: C192.2, R219.2
unnamed: C227.2, D39.A, Q43.B, R220.1, R222.2
unnamed: D39.C, Q43.E, R221.2
unnamed: C196.1, IC43.6, R225.2
unnamed: C195.1, R225.1
unnamed: C198.1, IC43.9
unnamed: IC43.12, Q44.1
unnamed: IC43.2, R223.1
unnamed: C199.2, IC43.4
unnamed: C227.1, Q43.C, Q45.3, R241.1
unnamed: C200.2, C202.1, L11.1, L12.2, R226.1, R243.2
unnamed: C204.1, D41.A, L13.1
unnamed: LED2.C, R228.1
unnamed: C210.2, R230.2
unnamed: C210.1, IC44.6, R231.2, R232.1
unnamed: C211.2, IC44.16
unnamed: IC44.5, R230.1
unnamed: IC44.7, R229.1
unnamed: C212.2, IC44.1
unnamed: C209.2, IC44.8
unnamed: C213.1, IC44.10
unnamed: IC44.2, R233.1, R234.2
unnamed: C217.2, R235.2
unnamed: C222.2, D46.A, FB9.P$1, IC45.1
unnamed: C221.1, D47.C, FB11.P$1, IC46.1
unnamed: IC47.6, IC48.4
unnamed: IC48.1, R236.1
unnamed: IC50.7, R237.2, R238.1
unnamed: IC43.8, R240.1
unnamed: R242.2, SW3.P$1
unnamed: C229.2, Q47.B, R244.1, R245.2, R246.2
unnamed: C231.2, Q47.C, R249.1, R251.2
unnamed: Q46.C, R246.1
unnamed: C230.1, Q46.B, R247.2, R248.1
unnamed: C231.1, Q48.B, R249.2, R250.2
unnamed: Q49.B, R251.1, R253.2
unnamed: C224.+, FB12.P$1, IC50.1, R237.1, R239.1
unnamed: R254.2, X21.16
unnamed: C236.2, IC37.10, R255.2
unnamed: C237.2, IC37.7, R256.2
unnamed: C238.2, IC37.11, R257.2
unnamed: C239.1, IC37.6, R258.2
unnamed: IC21.23, R126.2
NTC1: C125.2, MCU.A5, R129.1, X13.13
NTC2: C130.2, MCU.A6, R133.1, X15.13
NTC_IN: IC30.2, IC30.3, IC30.5, X12.7, X12.7.1
OUT1+: C106.1, J1.P$1, K_SER.12B, TP3.TIP
OUT1-: C107.2, C107.2.1, C109.2, J3.P$1, K_PAR.14B, K_S1.7, R124.1, TP3.GND, X13.17, X13.18, X13.19, X13.20, ZD8.A
OUT2+: C110.1, C111.1, C112.1, C112.1.1, J4.P$1, K_PAR.14A, K_S2.7, TP4.TIP, X15.23, X15.24, X15.25, X15.26, ZD9.C
OUT2-: C113.2, J5.P$1, K_SER.12A, TP4.GND
OUT+: C47.2, C50.1, C63.1, C79.1, Q5.E, Q6.E, Q17.E, R14.2, R28.2, R29.2, R35.1, R83.2, TP2.TIP, X3.23, X3.24, X3.25, X3.26, ZD3.C
OUT+1: C170.2, C175.1, C177.1, C229.1, Q34.E, Q39.E, Q47.E, R162.1, R220.2, R244.2, R259.2, R260.2, TP6.TIP, X21.23, X21.24, X21.25, X21.26, ZD16.C
OUT-: C46.1, C48.2, C83.2, Q19.E, R59.2, R64.1, R66.1, R97.1, X3.17, X3.18, X3.19, X3.20, ZD3.A
OUT-1: C172.2, C176.1, C230.2, Q46.E, R163.2, R207.1, R210.1, R247.1, X21.17, X21.18, X21.19, X21.20, ZD16.A
POST_OE: Q15.3, R53.1
POST_OE1: Q40.3, R196.1
POUT-: C13.2, C14.2, C15.2, C16.2, C19.1, R66.2, R68.1, SH1.P$1, TP1.GND
POUT-1: C200.1, C201.2, C202.2, C203.2, C226.2, R208.1, R210.2, SH4.P$1, TP5.GND
PREG_OUT: FB1.2, Q4.D, TP1.TIP
PREG_OUT1: FB10.2, Q31.D, TP5.TIP
PRE_OE: IC9.17, Q15.1, R3.2, R75.2
PRE_OE1: IC38.17, Q40.1, R192.2, R240.2
PS_MISO: IC9.3, IC14.15, X3.9
PS_MISO1: IC37.15, IC38.3, X21.9
PS_MOSI: IC9.2, IC11.7, IC14.16, X3.1
PS_MOSI1: IC36.7, IC37.16, IC38.2, X21.1
PS_SCLK: IC9.1, IC11.6, IC14.1, X3.7
PS_SCLK1: IC36.6, IC37.1, IC38.1, X21.7
PWRDIR: IC32.6, MCU.A1
PWRGOOD: IC5.5, IC9.16, R27.2
PWRGOOD1: IC38.16, IC50.5, R239.2
PWRSS: IC32.1, MCU.A2
PWR_DIRECT: Q29.3, X16.3
PWR_IN1+: C105.1, C107.1, C107.1.1, K_PAR.11A, K_S1.2, X13.23, X13.24, X13.25, X13.26, ZD8.C
PWR_IN2-: C112.2, C112.2.1, K_PAR.11B, K_S2.2, R128.1, X15.17, X15.18, X15.19, X15.20, ZD9.A
PWR_SSTART: Q30.3, X16.4
P_OUT: C14.1, C15.1, C16.1, FB1.1, L4.2, R6.2
P_OUT1: C201.1, C203.1, C226.1, FB10.1, L11.2, R226.2
Q4_OUT: Q4.S, R28.1, R30.2, R31.2, R34.2, ZD4.A
Q4_OUT1: Q31.S, R181.2, R183.2, R199.2, R259.1, ZD13.A
Q7C: Q10.B, Q10.C, Q11.B, Q13.C
Q7C1: Q33.C, Q36.B, Q36.C, Q37.B
Q9C: D13.C, Q9.2, Q9.4, ZD5.A
Q9C1: D37.C, Q35.2, Q35.4, ZD14.A
RTC_SELECT: IC27.6, MCU.8
SCLK: IC21.3, IC23.5, IC26.5, IC27.10, IC28.6, IC29.33, JP5.1, LCD1.36, MCU.ICSP_SCK, WIFI.5, X20.9
SENSE: IC1.10, Q1.3, R2.2
SENSE1: IC43.10, Q44.3, R224.2
SENSE1+: K_S1.4, X12.5, X12.5.1
SENSE1-: K_S1.5, X12.4, X12.4.1
SENSE1_IN+: K_S1.3, X13.22
SENSE1_IN-: K_S1.6, X13.21
SENSE2+: K_S2.5, X14.3, X14.3.1
SENSE2-: K_S2.4, X14.2, X14.2.1
SENSE2_IN+: K_S2.6, X15.22
SENSE2_IN-: K_S2.3, X15.21
SENSE+: C45.1, R35.2, R47.2, R88.1, X3.22
SENSE+1: C169.1, R162.2, R203.2, R245.1, X21.22
SENSE-: C51.1, R57.2, R59.1, R94.2, X3.21
SENSE-1: C171.1, R163.1, R204.2, R248.2, X21.21
SENSE_ERR: IC9.10, Q18.C, R92.1
SENSE_ERR1: IC38.10, Q49.C, R252.1
SENSE_PROT: Q11.C, Q12.C, Q16.C, R41.2, R48.2
SENSE_PROT1: Q37.C, Q38.C, Q48.C, R180.2, R197.2
SGND: C11.1, C21.2, C22.2, IC1.3, JP1.1, R7.2, R15.2, SH2.P$1
SGND1: C195.2, C196.2, C199.1, IC43.3, JP8.1, R218.2, R223.2, SH5.P$1
SW: C17.1, D5.3, L2.1, Q1.2, R4.1
SW1: C28.1, C32.1, D10.C, IC4.14, IC4.15, TR1.1
SW2: C86.1, C89.1, D19.C, IC16.14, IC16.15, L9.1
SW3: C192.1, D38.3, L16.1, Q44.2, R242.1
SW4: C211.1, C217.1, D40.C, IC44.14, IC44.15, TR3.1
SYNC: IC4.4, JP1.3, R21.1
SYNC1: IC23.2, IC35.7
SYNC2: IC24.2, IC35.1, IC35.2, IC35.3
SYNC3: IC44.4, JP8.3, R254.1
SYNC_IN: IC35.5, IC35.6, X16.7
TEMP_ANALOG: C129.2, MCU.A0, R132.1, X17.2
TEMP_FREQ1: IC31.3, R146.1
TEMP_NTC: NTC1.1, NTC1.1.1, X3.13
TEMP_NTC1: NTC2.1, NTC2.1.1, X21.13
TOCAP: C146.+, IC29.20
TOUCH_CS: LCD1.30, MCU.43
TOUCH_DIN: JP6.3, MCU.42
TOUCH_DOUT: JP7.3, MCU.3
TOUCH_IRQ: LCD1.34, MCU.2
TOUCH_SCLK: JP5.3, MCU.44
U_MON: IC6.7, R51.1, R52.1, R79.1
U_MON1: IC40.7, R165.1, R205.1, R255.1
U_SERVO: D15.C, D16.A, IC6.1, R54.2, R82.1
U_SERVO1: D31.A, D32.C, IC40.1, R190.1, R216.2
U_SET: IC13.5, R77.1
U_SET1: IC47.5, R257.1
U_SET_OUT: IC11.4, IC13.4, R49.1
U_SET_OUT1: IC36.4, IC47.4, R164.1
V+: C52.2, C53.1, C54.2, C55.2, C56.2, C65.1, C81.2, FB3.P$2, IC6.8, IC7.8, IC8.7, IC10.2, IC12.6, IC13.2, IC15.3, R81.1, R87.2
V+1: C158.2, C162.1, C168.2, C174.1, C180.2, C183.2, C184.2, FB11.P$2, IC39.7, IC40.8, IC41.8, IC42.2, IC47.2, IC48.6, IC49.3, R166.1, R189.2
V-: C57.2, C58.2, C59.1, C60.2, C61.2, C82.2, FB2.P$2, IC6.4, IC7.4, IC8.4, IC12.3, IC15.12, R99.1
V-1: C160.2, C173.2, C179.1, C181.2, C182.2, C185.2, FB9.P$2, IC39.4, IC40.4, IC41.4, IC48.3, IC49.12, R167.1
VIN: B1.+, C88.+, IC17.1, L8.1
VOUT+: C34.1, C37.1, C38.1, IC4.11, L7.1, R19.1, TR1.3
VOUT+1: C206.1, C215.1, C216.1, IC44.11, L14.1, R231.1, TR3.3
VOUT-: D7.C, TR1.2
VOUT-1: D41.C, TR3.2
WATCHDOG: MCU.5, R152.2
WIFI_CE: MCU.4, WIFI.3
XUSB_GND: C101.2, C102.1, C104.2, FB7.P$2, IC19.1, IC20.2, IC20.8, X9.4, X11.4
XUSB_VBUS: C102.2, FB6.P$1, IC19.4, X9.1, X11.1
